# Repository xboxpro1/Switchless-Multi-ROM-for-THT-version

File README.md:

# CBM Switchless Multi-ROM for 2364 & 27128 & 27256 ROMs

This is a fork, rework and combination of two repositories from RetroNynjah.

<https://github.com/RetroNynjah/Switchless-Multi-ROM-for-2364>

<https://github.com/RetroNynjah/Switchless-Multi-ROM-for-27128-27256>

I would like to thank RetroNynjah for the brilliant idea and excellent work.<br/>
After a long search on the internet, there is finally the perfect ROM switcher.

<br/>
<br/>

A switchless multi-ROM for 2364 ROM (24-pin) and 27128/27256 ROM (28-pin) type applications. <br/>
The switch is controlled by an MCU that is picking up predefined magic words on the data bus.  

Example use cases:
* Menu driven Kernal switch for Commodore VIC-20
* Menu driven Kernal switch for Commodore C64 (longboards)
* Menu driven Kernal switch for Commodore C64C (shortboard)
* Menu driven Kernal switch for Commodore C128
* You tell me

Check the General-Info.pdf for a general description and BOM.

Check the Application-Info.pdf in the applications folder for examples on how to use it for the use cases above.

Check the Hardware-Info.pdf and SMD-Hardware-Info.pdf in the hardware folder for a general technical description and build instructions.

A short video that shows how it works can be seen here. 
<https://youtu.be/isT9-QBMzEc?si=csgdmX4p8TZYezGX>

  <br/>
  <br/>

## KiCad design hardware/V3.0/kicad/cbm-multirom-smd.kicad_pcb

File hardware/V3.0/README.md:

# CBM Switchless Multi-ROM for 2364 & 27128 & 27256 ROMs

This is a fork, rework and combination of two repositories from RetroNynjah.

<br/>

Here are the files to make the SMD hardware and the shematic.

Check the SMD-Hardware-Info.pdf in the hardware folder for a general technical description and build instructions.

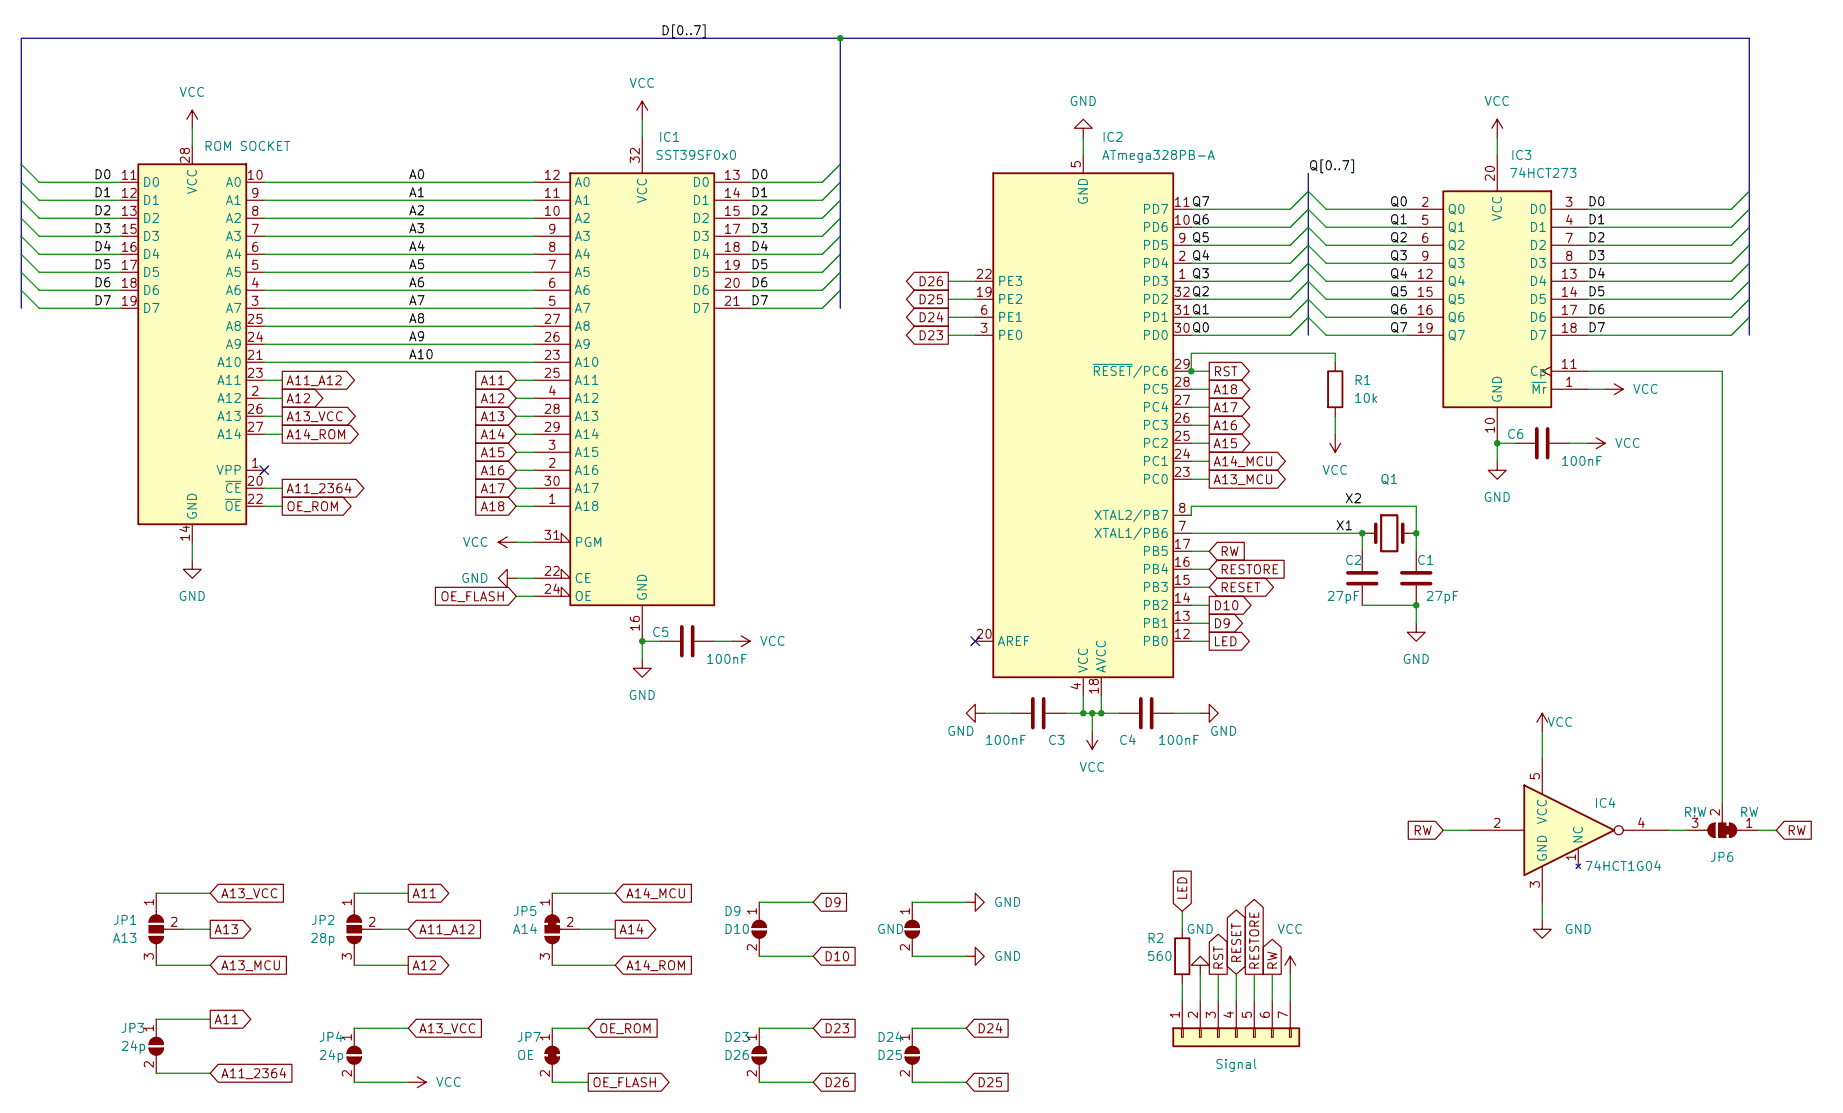
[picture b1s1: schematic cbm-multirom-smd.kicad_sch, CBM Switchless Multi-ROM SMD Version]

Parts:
C1, C2: 27pF; C_0805_2012Metric_Pad1.18x1.45mm_HandSolder
C3, C4, C5, C6: 100nF; C_0805_2012Metric_Pad1.18x1.45mm_HandSolder
Con1: Signal; PinHeader_1x07_P2.54mm_Horizontal
D9: D10; SolderJumper-2_P1.3mm_Open_RoundedPad1.0x1.5mm
D23: D26; SolderJumper-2_P1.3mm_Open_RoundedPad1.0x1.5mm
D24: D25; SolderJumper-2_P1.3mm_Open_RoundedPad1.0x1.5mm
GND1: GND; SolderJumper-2_P1.3mm_Open_RoundedPad1.0x1.5mm
IC1: SST39SF0x0; PLCC-32_SMD-Socket
IC2: 328P(B); TQFP-32_7x7mm_P0.8mm
IC3: 74HCT273; SO-20_12.8x7.5mm_P1.27mm
IC4: 74HCT1G04; SOT-23-5_HandSoldering
JP1: A13; SolderJumper-3_P1.3mm_Open_RoundedPad1.0x1.5mm
JP2: 28p; SolderJumper-3_P1.3mm_Open_RoundedPad1.0x1.5mm
JP3, JP4: 24p; SolderJumper-2_P1.3mm_Open_RoundedPad1.0x1.5mm
JP5: A14; SolderJumper-3_P1.3mm_Bridged12_RoundedPad1.0x1.5mm
JP6: RW; SolderJumper-3_P1.3mm_Bridged12_RoundedPad1.0x1.5mm
JP7: OE; SolderJumper-2_P1.3mm_Bridged_RoundedPad1.0x1.5mm
Q1: 20MHz; Crystal_SMD_HC49-SD
R1: 10k; R_0805_2012Metric_Pad1.20x1.40mm_HandSolder
R2: 560; R_0805_2012Metric_Pad1.20x1.40mm_HandSolder
ROM1: ROM SOCKET; RomAdapter_28_P

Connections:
/A0: IC1.12 (A0), ROM1.10 (A0)
/A1: IC1.11 (A1), ROM1.9 (A1)
/A2: IC1.10 (A2), ROM1.8 (A2)
/A3: IC1.9 (A3), ROM1.7 (A3)
/A4: IC1.8 (A4), ROM1.6 (A4)
/A5: IC1.7 (A5), ROM1.5 (A5)
/A6: IC1.6 (A6), ROM1.4 (A6)
/A7: IC1.5 (A7), ROM1.3 (A7)
/A8: IC1.27 (A8), ROM1.25 (A8)
/A9: IC1.26 (A9), ROM1.24 (A9)
/A10: IC1.23 (A10), ROM1.21 (A10)
/D0: IC1.13 (D0), IC3.3 (D0), ROM1.11 (D0)
/D1: IC1.14 (D1), IC3.4 (D1), ROM1.12 (D1)
/D2: IC1.15 (D2), IC3.7 (D2), ROM1.13 (D2)
/D3: IC1.17 (D3), IC3.8 (D3), ROM1.15 (D3)
/D4: IC1.18 (D4), IC3.13 (D4), ROM1.16 (D4)
/D5: IC1.19 (D5), IC3.14 (D5), ROM1.17 (D5)
/D6: IC1.20 (D6), IC3.17 (D6), ROM1.18 (D6)
/D7: IC1.21 (D7), IC3.18 (D7), ROM1.19 (D7)
/Q0: IC2.30 (PD0), IC3.2 (Q0)
/Q1: IC2.31 (PD1), IC3.5 (Q1)
/Q2: IC2.32 (PD2), IC3.6 (Q2)
/Q3: IC2.1 (PD3), IC3.9 (Q3)
/Q4: IC2.2 (PD4), IC3.12 (Q4)
/Q5: IC2.9 (PD5), IC3.15 (Q5)
/Q6: IC2.10 (PD6), IC3.16 (Q6)
/Q7: IC2.11 (PD7), IC3.19 (Q7)
/X1: C2.1, IC2.7 (XTAL1/PB6), Q1.1
/X2: C1.1, IC2.8 (XTAL2/PB7), Q1.2
A11: IC1.25 (A11), JP2.1 (A), JP3.1 (A)
A11_2364: JP3.2 (B), ROM1.20 (~CE)
A11_A12: JP2.2 (C), ROM1.23 (A11)
A12: IC1.4 (A12), JP2.3 (B), ROM1.2 (A12)
A13: IC1.28 (A13), JP1.2 (C)
A13_MCU: IC2.23 (PC0), JP1.3 (B)
A13_VCC: JP1.1 (A), JP4.1 (A), ROM1.26 (A13)
A14: IC1.29 (A14), JP5.2 (C)
A14_MCU: IC2.24 (PC1), JP5.1 (A)
A14_ROM: JP5.3 (B), ROM1.27 (A14)
A15: IC1.3 (A15), IC2.25 (PC2)
A16: IC1.2 (A16), IC2.26 (PC3)
A17: IC1.30 (A17), IC2.27 (PC4)
A18: IC1.1 (A18), IC2.28 (PC5)
D9: D9.1 (A), IC2.13 (PB1)
D10: D9.2 (B), IC2.14 (PB2)
D23: D23.1 (A), IC2.3 (PE0)
D24: D24.1 (A), IC2.6 (PE1)
D25: D24.2 (B), IC2.19 (PE2)
D26: D23.2 (B), IC2.22 (PE3)
GND: C1.2, C2.2, C3.2, C4.2, C5.2, C6.2, Con1.2, GND1.1 (A), GND1.2 (B), IC1.16 (GND), IC1.22 (CE), IC2.5 (GND), IC2.21 (GND), IC3.10 (GND), IC4.3 (GND), ROM1.14 (GND)
LED: IC2.12 (PB0), R2.1
unnamed: Con1.1, R2.2
unnamed: IC3.11 (Cp), JP6.2 (C)
unnamed: IC4.4, JP6.3 (B)
OE_FLASH: IC1.24 (OE), JP7.2 (B)
OE_ROM: JP7.1 (A), ROM1.22 (~OE)
RESET: Con1.4, IC2.15 (PB3)
RESTORE: Con1.5, IC2.16 (PB4)
RST: Con1.3, IC2.29 (~RESET/PC6), R1.1
RW: Con1.6, IC2.17 (PB5), IC4.2, JP6.1 (A)
VCC: C3.1, C4.1, C5.1, C6.1, Con1.7, IC1.31 (PGM), IC1.32 (VCC), IC2.4 (VCC), IC2.18 (AVCC), IC3.1 (~Mr), IC3.20 (VCC), IC4.5 (VCC), JP4.2 (B), R1.2, ROM1.28 (VCC)

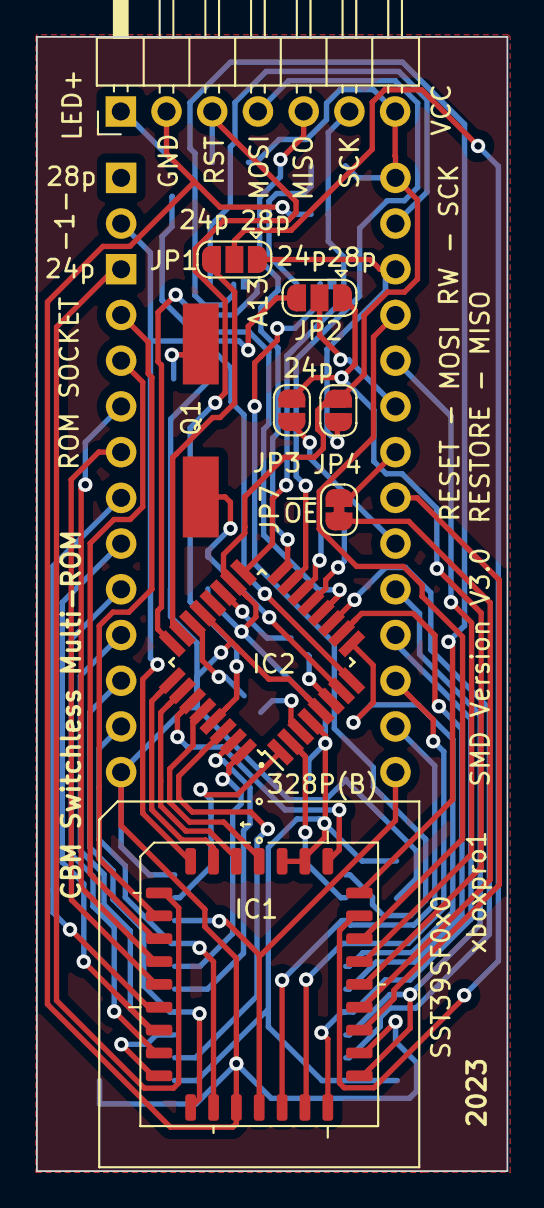
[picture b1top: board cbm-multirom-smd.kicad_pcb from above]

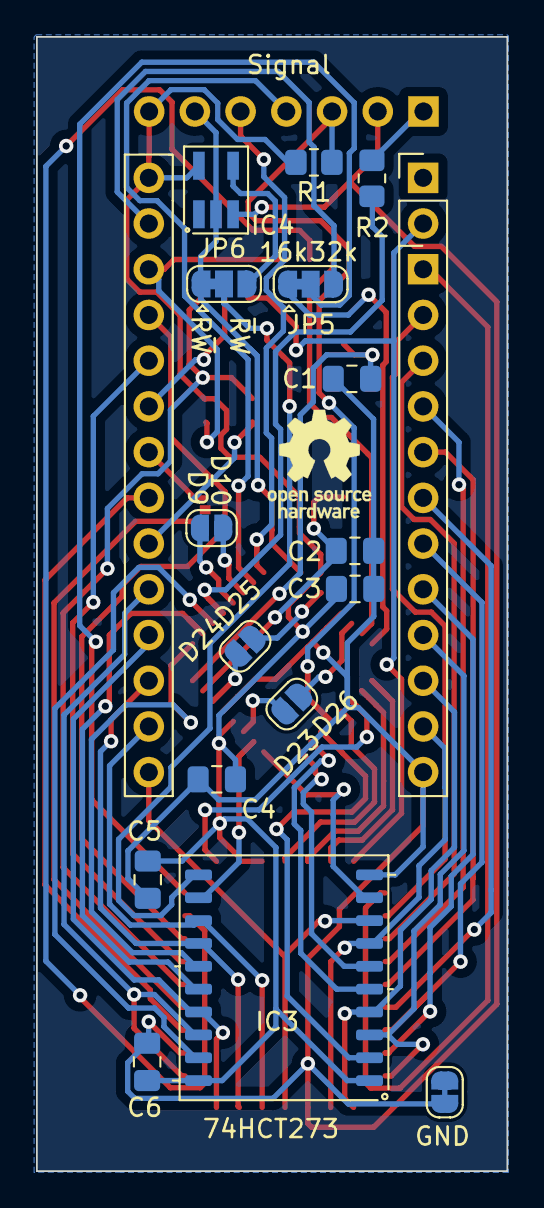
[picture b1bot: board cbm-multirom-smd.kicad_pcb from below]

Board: 2 copper layers, 26.1 x 63.0 mm, 26 parts (16 on the bottom side), 61 nets.

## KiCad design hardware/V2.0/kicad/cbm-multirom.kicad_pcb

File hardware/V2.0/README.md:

# CBM Switchless Multi-ROM for 2364 & 27128 & 27256 ROMs

This is a fork, rework and combination of two repositories from RetroNynjah.

<br/>

Here are the files to make the THT hardware and the shematic.

Check the Hardware-Info.pdf in the hardware folder for a general technical description and build instructions.

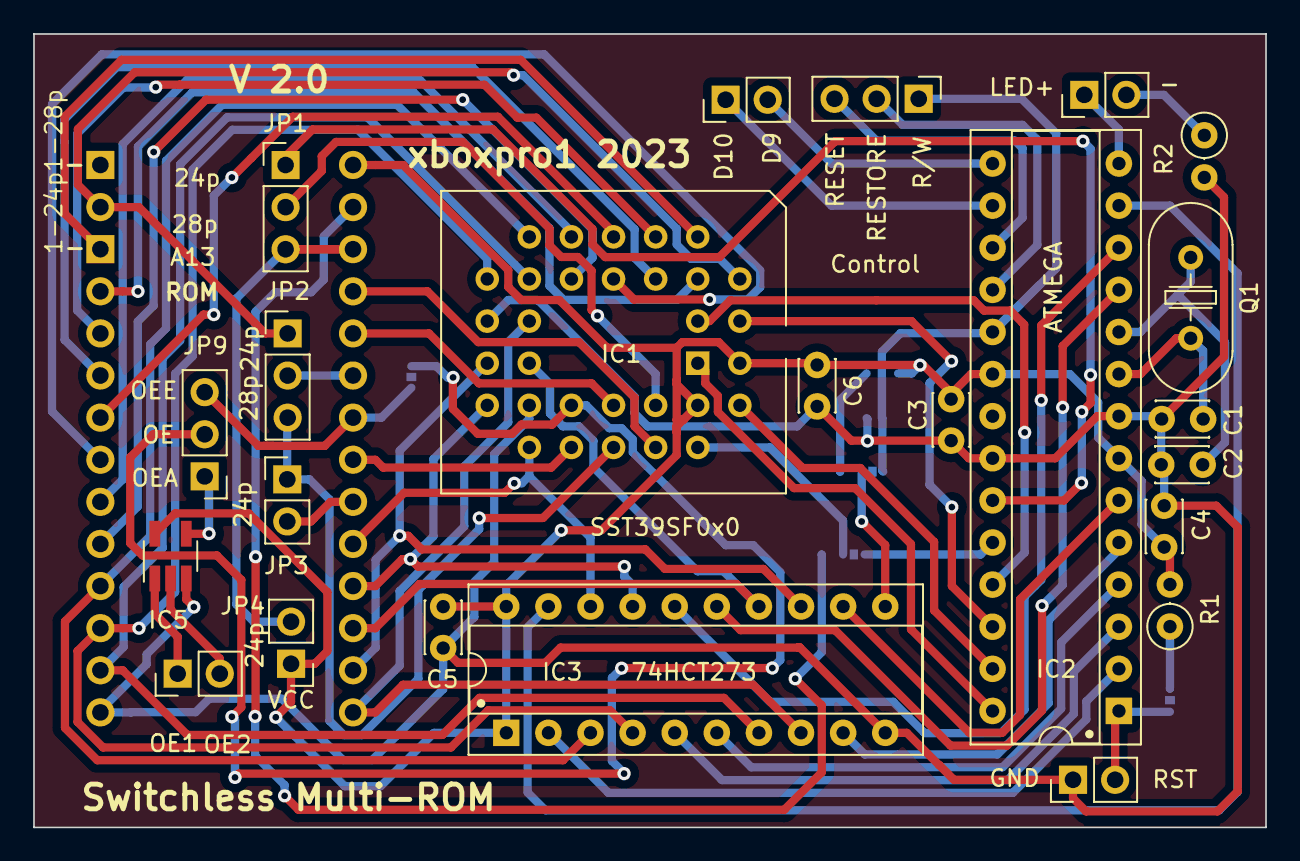
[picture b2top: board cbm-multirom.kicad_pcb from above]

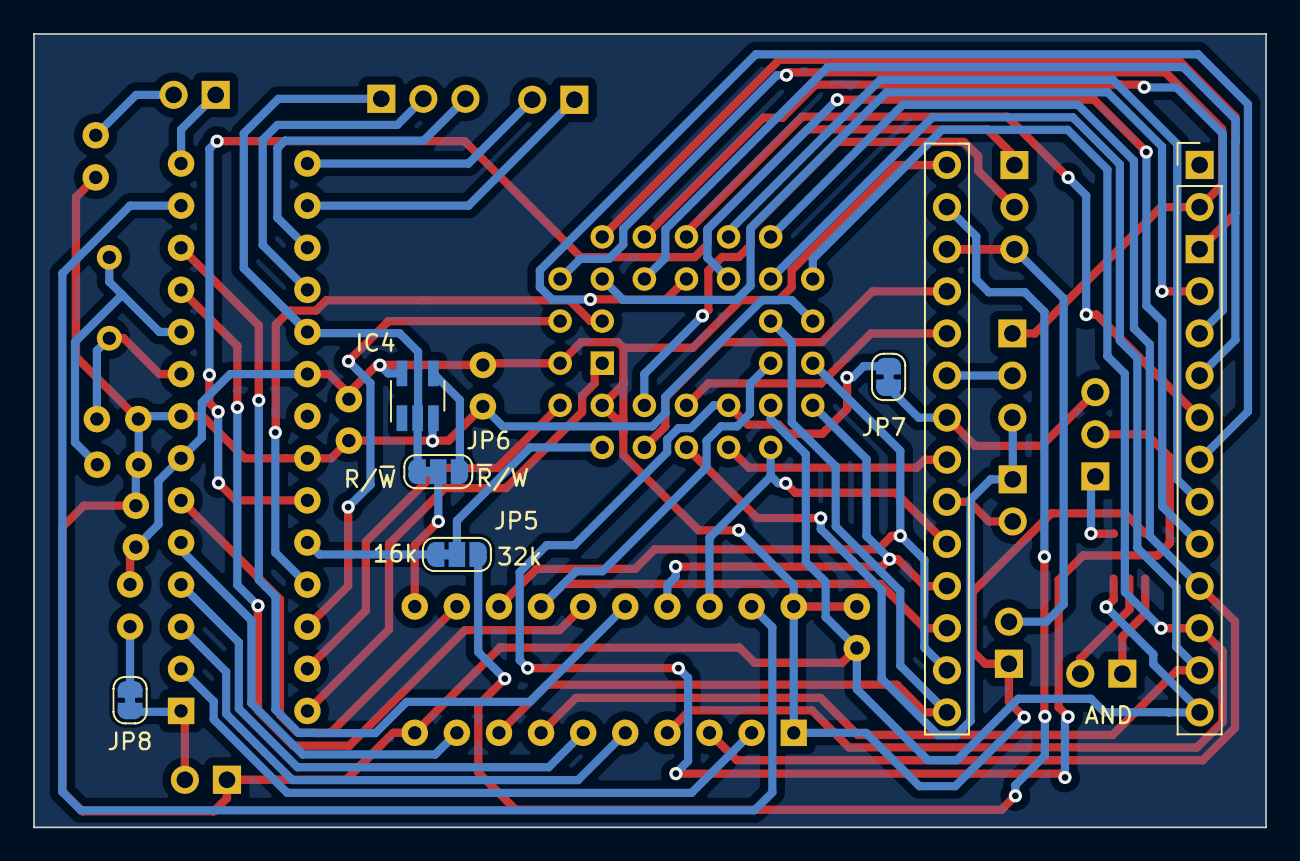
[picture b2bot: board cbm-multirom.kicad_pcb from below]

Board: 2 copper layers, 74.3 x 47.9 mm, 29 parts (5 on the bottom side), 32 nets.

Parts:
AND: PinHeader_1x02_P2.54mm_Vertical
C1, C2: 30p; C_Disc_D3.0mm_W2.0mm_P2.50mm
C3, C4, C5, C6: 100; C_Disc_D3.0mm_W2.0mm_P2.50mm
Control: PinHeader_1x03_P2.54mm_Vertical
IC1: PLCC-32_THT-Socket
IC2: DIP-28_W7.62mm_Socket
IC3: DIP-20_W7.62mm_Socket
IC4, IC5: SOT-23-5_HandSoldering
JP1, JP2, JP9: PinHeader_1x03_P2.54mm_Vertical
JP3, JP4: PinHeader_1x02_P2.54mm_Vertical
JP5, JP6: SolderJumper-3_P1.3mm_Bridged12_RoundedPad1.0x1.5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; SolderJumper-3_P1.3mm_Bridged12_RoundedPad1.0x1.5mm_NumberL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
JP7, JP8: RST; SolderJumper-2_P1.3mm_Bridged_RoundedPad1.0x1.5mm
LED+: PinHeader_1x02_P2.54mm_Vertical
PinD: PinHeader_1x02_P2.54mm_Vertical
Q1: 20MHz; Crystal_HC49-4H_Vertical
R1, R2: 100k; R_Axial_DIN0207_L6.3mm_D2.5mm_P2.54mm_Vertical
ROM: RomAdapter_28_P
RSTC: PinHeader_1x02_P2.54mm_Vertical

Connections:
/A5: IC1.7, ROM.5
/D5: IC3.14, ROM.17
/D7: IC1.21, ROM.19
/Q7: IC2.13, IC3.19
A11: IC1.25, JP2.3, JP3.1
A11_A12: JP2.2, ROM.23
A12: IC1.4, JP2.1, ROM.2
A13: IC1.28, JP1.2
A13_Select: IC2.23, JP1.1
A13_VCC: JP1.3, JP4.2, ROM.26
A14: IC1.29, JP5.2
A14_27256: JP5.3, ROM.27
A14_Select: IC2.24, JP5.1
A15: IC1.3, IC2.25
A16: IC1.2, IC2.26
A17: IC1.30, IC2.27
A18: IC1.1, IC2.28
And1: AND.1, IC5.1
And2: AND.2, IC5.2
GND: C1.2, C2.2, C3.2, C4.2, C5.1, C6.1, IC1.16, IC1.22, IC2.8, IC2.22, IC3.10, IC4.3, IC5.3, R2.2, ROM.14, RSTC.1
JRST: JP8.2, R1.1
LED: IC2.14, LED+.1
OE: IC1.24, JP7.2, JP9.2
OEA: IC5.4, JP9.1
OEE: JP7.1, JP9.3, ROM.22
RESET: Control.3, IC2.17
RESTORE: Control.2, IC2.18
RST: IC2.1, JP8.1, RSTC.2
RW: Control.1, IC2.19, IC4.2, JP6.1
RWB: IC3.11, JP6.2
RWI: IC4.4, JP6.3
VCC: C3.1, C4.1, C5.2, C6.2, IC1.31, IC1.32, IC2.7, IC2.20, IC3.1, IC3.20, IC4.5, IC5.5, JP4.1, R1.2, ROM.28

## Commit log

2023-09-26 V2.0
    THT Version
2023-09-27 V2.0
    Del images
2023-09-29 V2.0
    IC4 - Floppy
2023-09-29 V2.0
    IC4 Floppy Disk
2023-09-29 V2.0
    Changed Info
2023-10-03 Version 2.0
    Changed firmware for MCU PB variants.
2023-10-03 V3.0
    Added hardware SMD PCB V3.0
2023-10-03 V3.0
    Added SMD V3.0 hardware
2023-10-03 V3.0
    Added V3.0 SMD hardware
2023-10-03 V3.0
    Renamed source file
2023-10-03 V3.0
    Update jumper settings.
2023-10-03 V3.0
    Changed Jumper setup
2023-10-04 V3.0
